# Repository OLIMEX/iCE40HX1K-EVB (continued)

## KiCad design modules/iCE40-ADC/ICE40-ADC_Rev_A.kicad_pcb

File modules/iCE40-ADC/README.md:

# Repository re-located here: https://github.com/OLIMEX/iCE40-ADC/tree/master

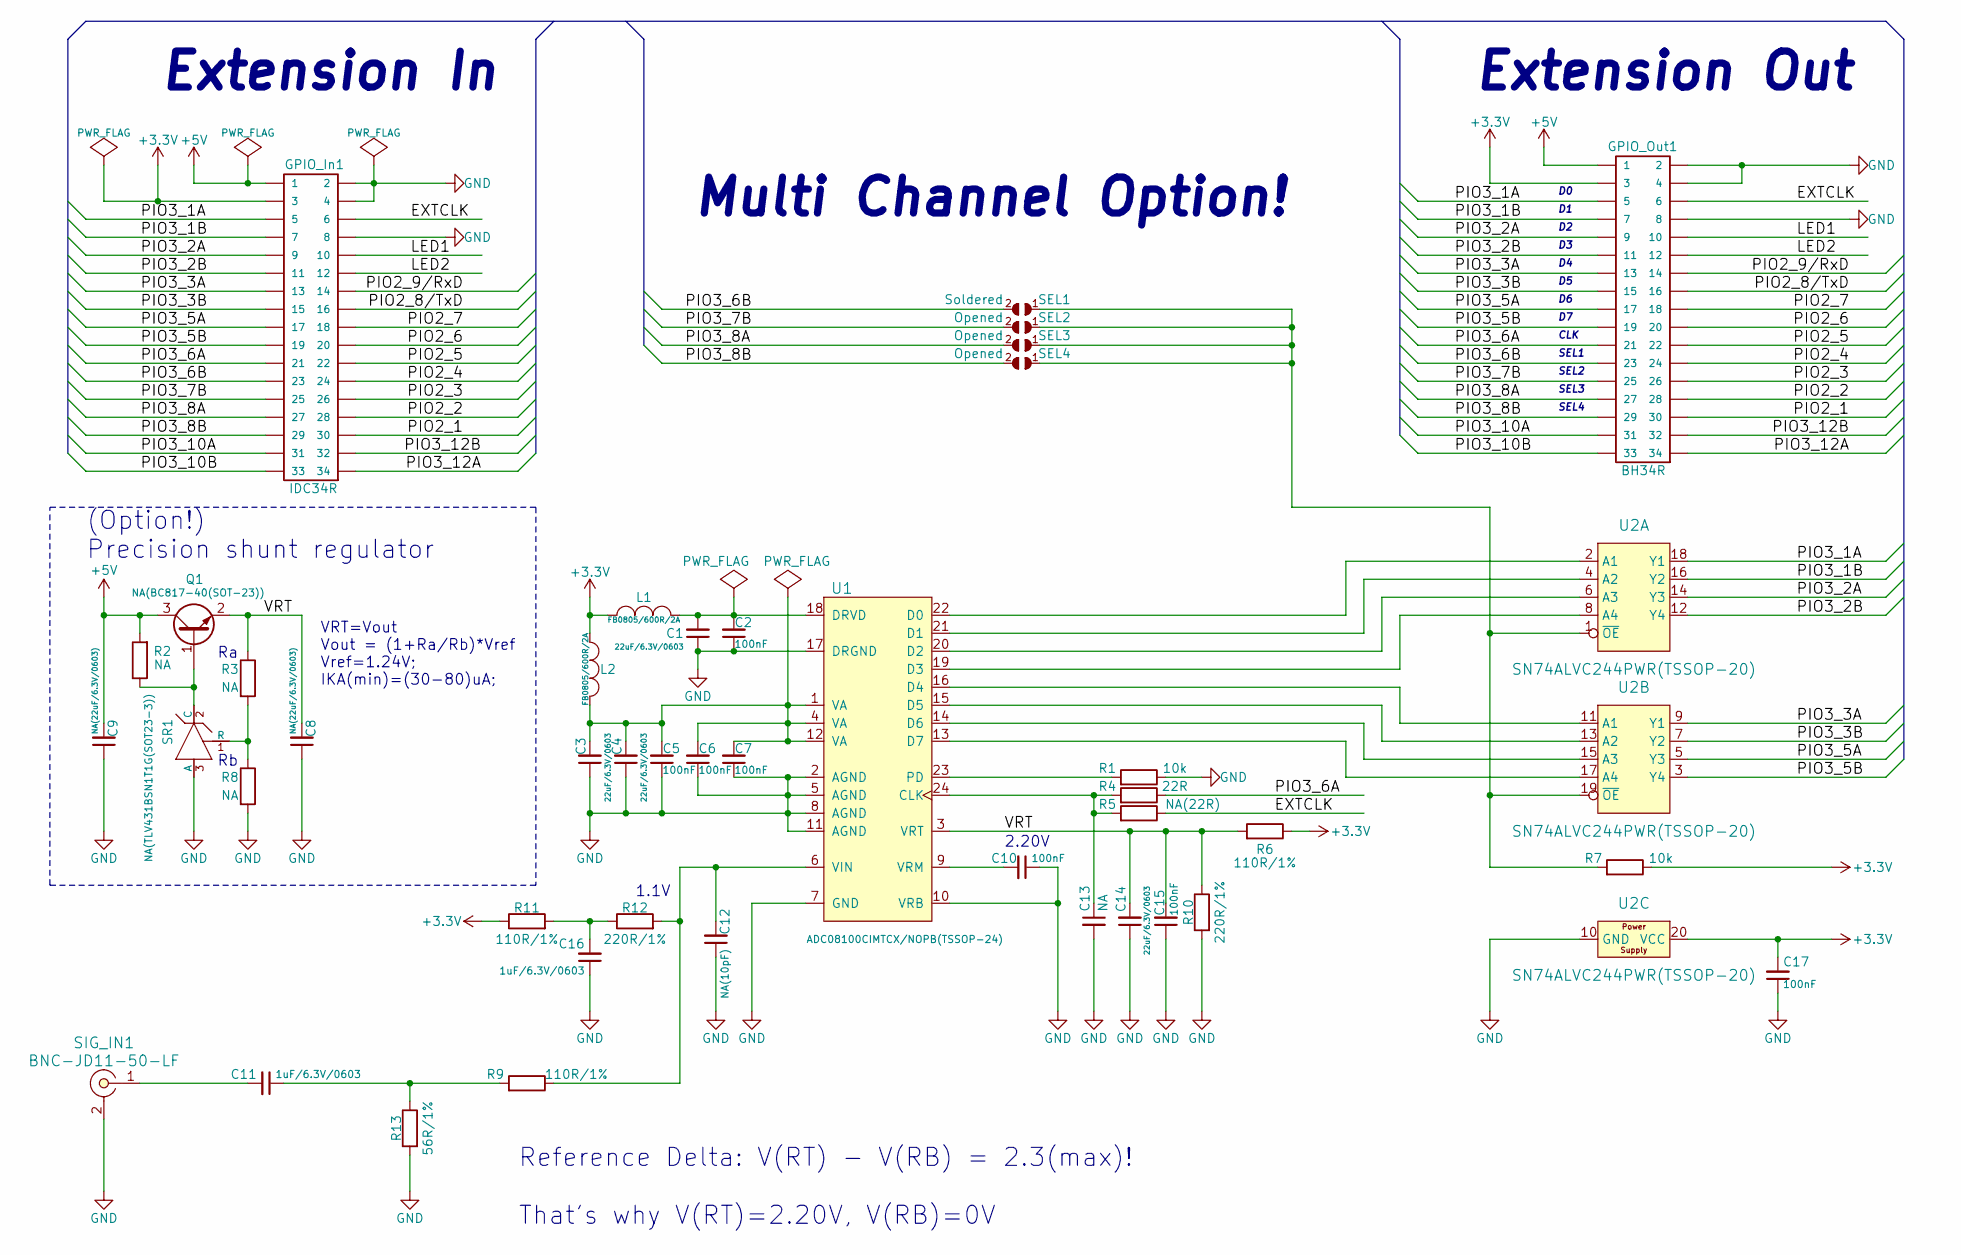
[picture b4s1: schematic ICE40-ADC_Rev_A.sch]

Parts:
C1, C3, C4, C14: 22uF/6.3V/0603; C_0603_5MIL_DWS
C2, C5, C6, C7, C10, C15, C17: 100nF; C_0402_5MIL_DWS
C8, C9: NA(22uF/6.3V/0603); C_0603_5MIL_DWS
C11, C16: 1uF/6.3V/0603; C_0603_5MIL_DWS
C12: NA(10pF); C_0402_5MIL_DWS
C13: NA; C_0402_5MIL_DWS
GPIO_In1: IDC34R; IDC34R_PCB
GPIO_Out1: BH34R
L1, L2: FB0805/600R/2A; L_0805_5MIL_DWS
Q1: NA(BC817-40(SOT-23)); SOT23
R1, R7: 10k; R_0402_5MIL_DWS
R2, R3, R8: NA; R_0402_5MIL_DWS
R4: 22R; R_0402_5MIL_DWS
R5: NA(22R); R_0402_5MIL_DWS
R6, R9, R11: 110R/1%; R_0402_5MIL_DWS
R10, R12: 220R/1%; R_0402_5MIL_DWS
R13: 56R/1%; R_0402_5MIL_DWS
SEL1: Soldered; SJ
SEL2, SEL3, SEL4: Opened; SJ
SIG_IN1: BNC-JD11-50-LF; BNC-JD11-50-LF_1-IN_2-GND
SR1: NA(TLV431BSN1T1G(SOT23-3)); SOT-23
U1: ADC08100CIMTCX/NOPB(TSSOP-24); TSSOP-24_Pitch-0.65mm_7.80x6.40x1.20mm
U2: SN74ALVC244PWR(TSSOP-20); TSSOP20_Pitch-0.65mm_6.6x4.5x1.2mm

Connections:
+3V3: C17.2, GPIO_In1.3, GPIO_Out1.3, L1.2, L2.2, R6.1, R7.1, R11.1, U2.20 (VCC)
+5V: C9.2, GPIO_In1.1, GPIO_Out1.1, Q1.3 (C), R2.2
/EXTCLK: GPIO_In1.6, GPIO_Out1.6, R5.1
/LED1: GPIO_In1.10, GPIO_Out1.10
/LED2: GPIO_In1.12, GPIO_Out1.12
/PIO2_1: GPIO_In1.30, GPIO_Out1.30
/PIO2_2: GPIO_In1.28, GPIO_Out1.28
/PIO2_3: GPIO_In1.26, GPIO_Out1.26
/PIO2_4: GPIO_In1.24, GPIO_Out1.24
/PIO2_5: GPIO_In1.22, GPIO_Out1.22
/PIO2_6: GPIO_In1.20, GPIO_Out1.20
/PIO2_7: GPIO_In1.18, GPIO_Out1.18
/PIO2_8/TxD: GPIO_In1.16, GPIO_Out1.16
/PIO2_9/RxD: GPIO_In1.14, GPIO_Out1.14
/PIO3_1A: GPIO_In1.5, GPIO_Out1.5, U2.18 (Y1)
/PIO3_1B: GPIO_In1.7, GPIO_Out1.7, U2.16 (Y2)
/PIO3_2A: GPIO_In1.9, GPIO_Out1.9, U2.14 (Y3)
/PIO3_2B: GPIO_In1.11, GPIO_Out1.11, U2.12 (Y4)
/PIO3_3A: GPIO_In1.13, GPIO_Out1.13, U2.9 (Y1)
/PIO3_3B: GPIO_In1.15, GPIO_Out1.15, U2.7 (Y2)
/PIO3_5A: GPIO_In1.17, GPIO_Out1.17, U2.5 (Y3)
/PIO3_5B: GPIO_In1.19, GPIO_Out1.19, U2.3 (Y4)
/PIO3_6A: GPIO_In1.21, GPIO_Out1.21, R4.1
/PIO3_6B: GPIO_In1.23, GPIO_Out1.23, SEL1.2
/PIO3_7B: GPIO_In1.25, GPIO_Out1.25, SEL2.2
/PIO3_8A: GPIO_In1.27, GPIO_Out1.27, SEL3.2
/PIO3_8B: GPIO_In1.29, GPIO_Out1.29, SEL4.2
/PIO3_10A: GPIO_In1.31, GPIO_Out1.31
/PIO3_10B: GPIO_In1.33, GPIO_Out1.33
/PIO3_12A: GPIO_In1.34, GPIO_Out1.34
/PIO3_12B: GPIO_In1.32, GPIO_Out1.32
/VRT: C8.2, C14.2, C15.2, Q1.2 (E), R3.1, R6.2, R10.1, U1.3 (VRT)
GND: C1.1, C2.1, C3.1, C4.1, C5.1, C6.1, C7.1, C8.1, C9.1, C10.1, C12.1, C13.2, C14.1, C15.1, C16.1, C17.1, GPIO_In1.2, GPIO_In1.4, GPIO_In1.8, GPIO_Out1.2, GPIO_Out1.4, GPIO_Out1.8, R1.1, R8.2, R10.2, R13.2, SIG_IN1.2, SR1.3 (A), U1.2 (AGND), U1.5 (AGND), U1.7 (GND), U1.8 (AGND), U1.10 (VRB), U1.11 (AGND), U1.17 (DRGND), U2.10 (GND)
unnamed: C1.2, C2.2, L1.1, U1.18 (DRVD)
unnamed: C3.2, C4.2, C5.2, C6.2, C7.2, L2.1, U1.1 (VA), U1.4 (VA), U1.12 (VA)
unnamed: C10.2, U1.9 (VRM)
unnamed: C11.1, R9.2, R13.1
unnamed: C11.2, SIG_IN1.1
unnamed: C12.2, R9.1, R12.2, U1.6 (VIN)
unnamed: C13.1, R4.2, R5.2, U1.24 (CLK)
unnamed: C16.2, R11.2, R12.1
unnamed: Q1.1 (B), R2.1, SR1.2 (C)
unnamed: R1.2, U1.23 (PD)
unnamed: R3.2, R8.1, SR1.1 (R)
unnamed: R7.2, SEL1.1, SEL2.1, SEL3.1, SEL4.1, U2.1 (~OE), U2.19 (~OE)
unnamed: U1.13 (D7), U2.17 (A4)
unnamed: U1.14 (D6), U2.15 (A3)
unnamed: U1.15 (D5), U2.13 (A2)
unnamed: U1.16 (D4), U2.11 (A1)
unnamed: U1.19 (D3), U2.8 (A4)
unnamed: U1.20 (D2), U2.6 (A3)
unnamed: U1.21 (D1), U2.4 (A2)
unnamed: U1.22 (D0), U2.2 (A1)

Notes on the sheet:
Extension Out
Extension In
VRT=Vout Vout = (1+Ra/Rb)*Vref Vref=1.24V; IKA(min)=(30-80)uA;
2.20V
1.1V
Reference Delta: V(RT) - V(RB) = 2.3(max)! That's why V(RT)=2.20V, V(RB)=0V
(Option!) Precision shunt regulator
Multi Channel Option!
CLK
SEL1
SEL2
SEL3
SEL4

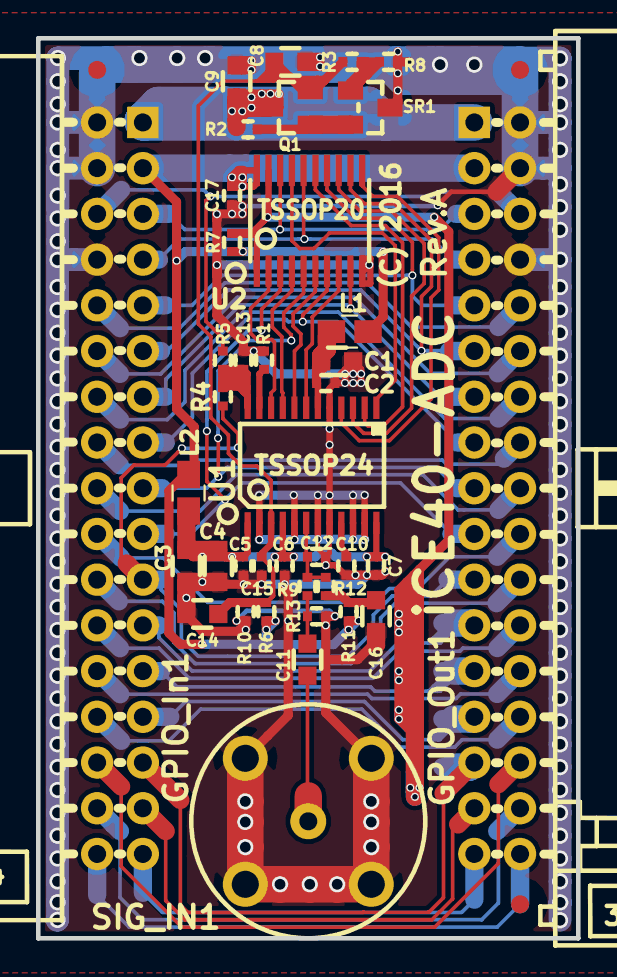
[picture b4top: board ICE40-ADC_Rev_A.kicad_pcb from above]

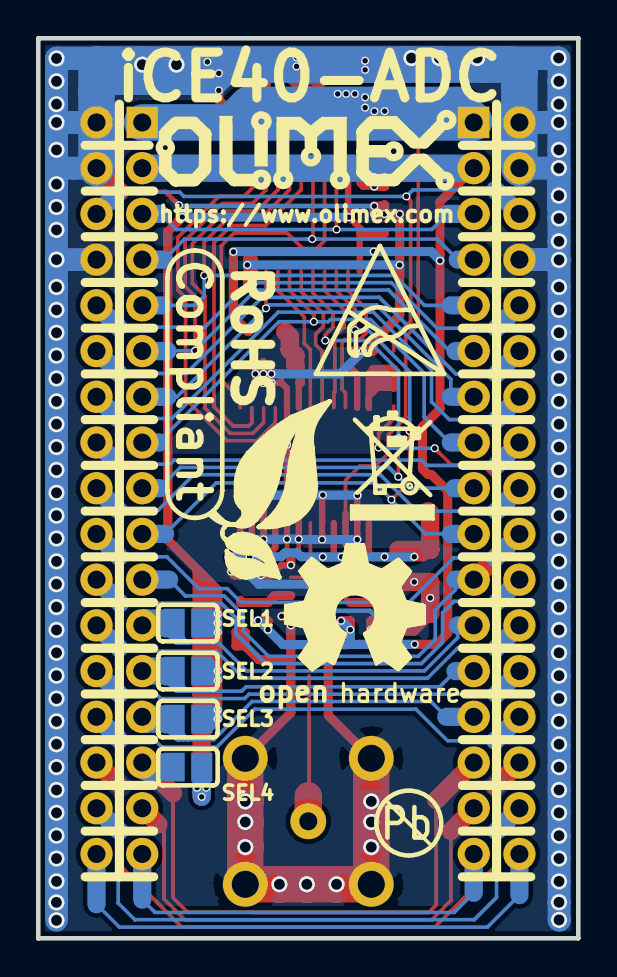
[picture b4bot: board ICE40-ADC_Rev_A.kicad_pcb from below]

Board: 2 copper layers, 30.0 x 50.0 mm, 45 parts (6 on the bottom side), 53 nets.

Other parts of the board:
Ref**: Val**; LOGO_ANTISTATIC_1
Ref**#2: Val**; LOGO_ROHS_1

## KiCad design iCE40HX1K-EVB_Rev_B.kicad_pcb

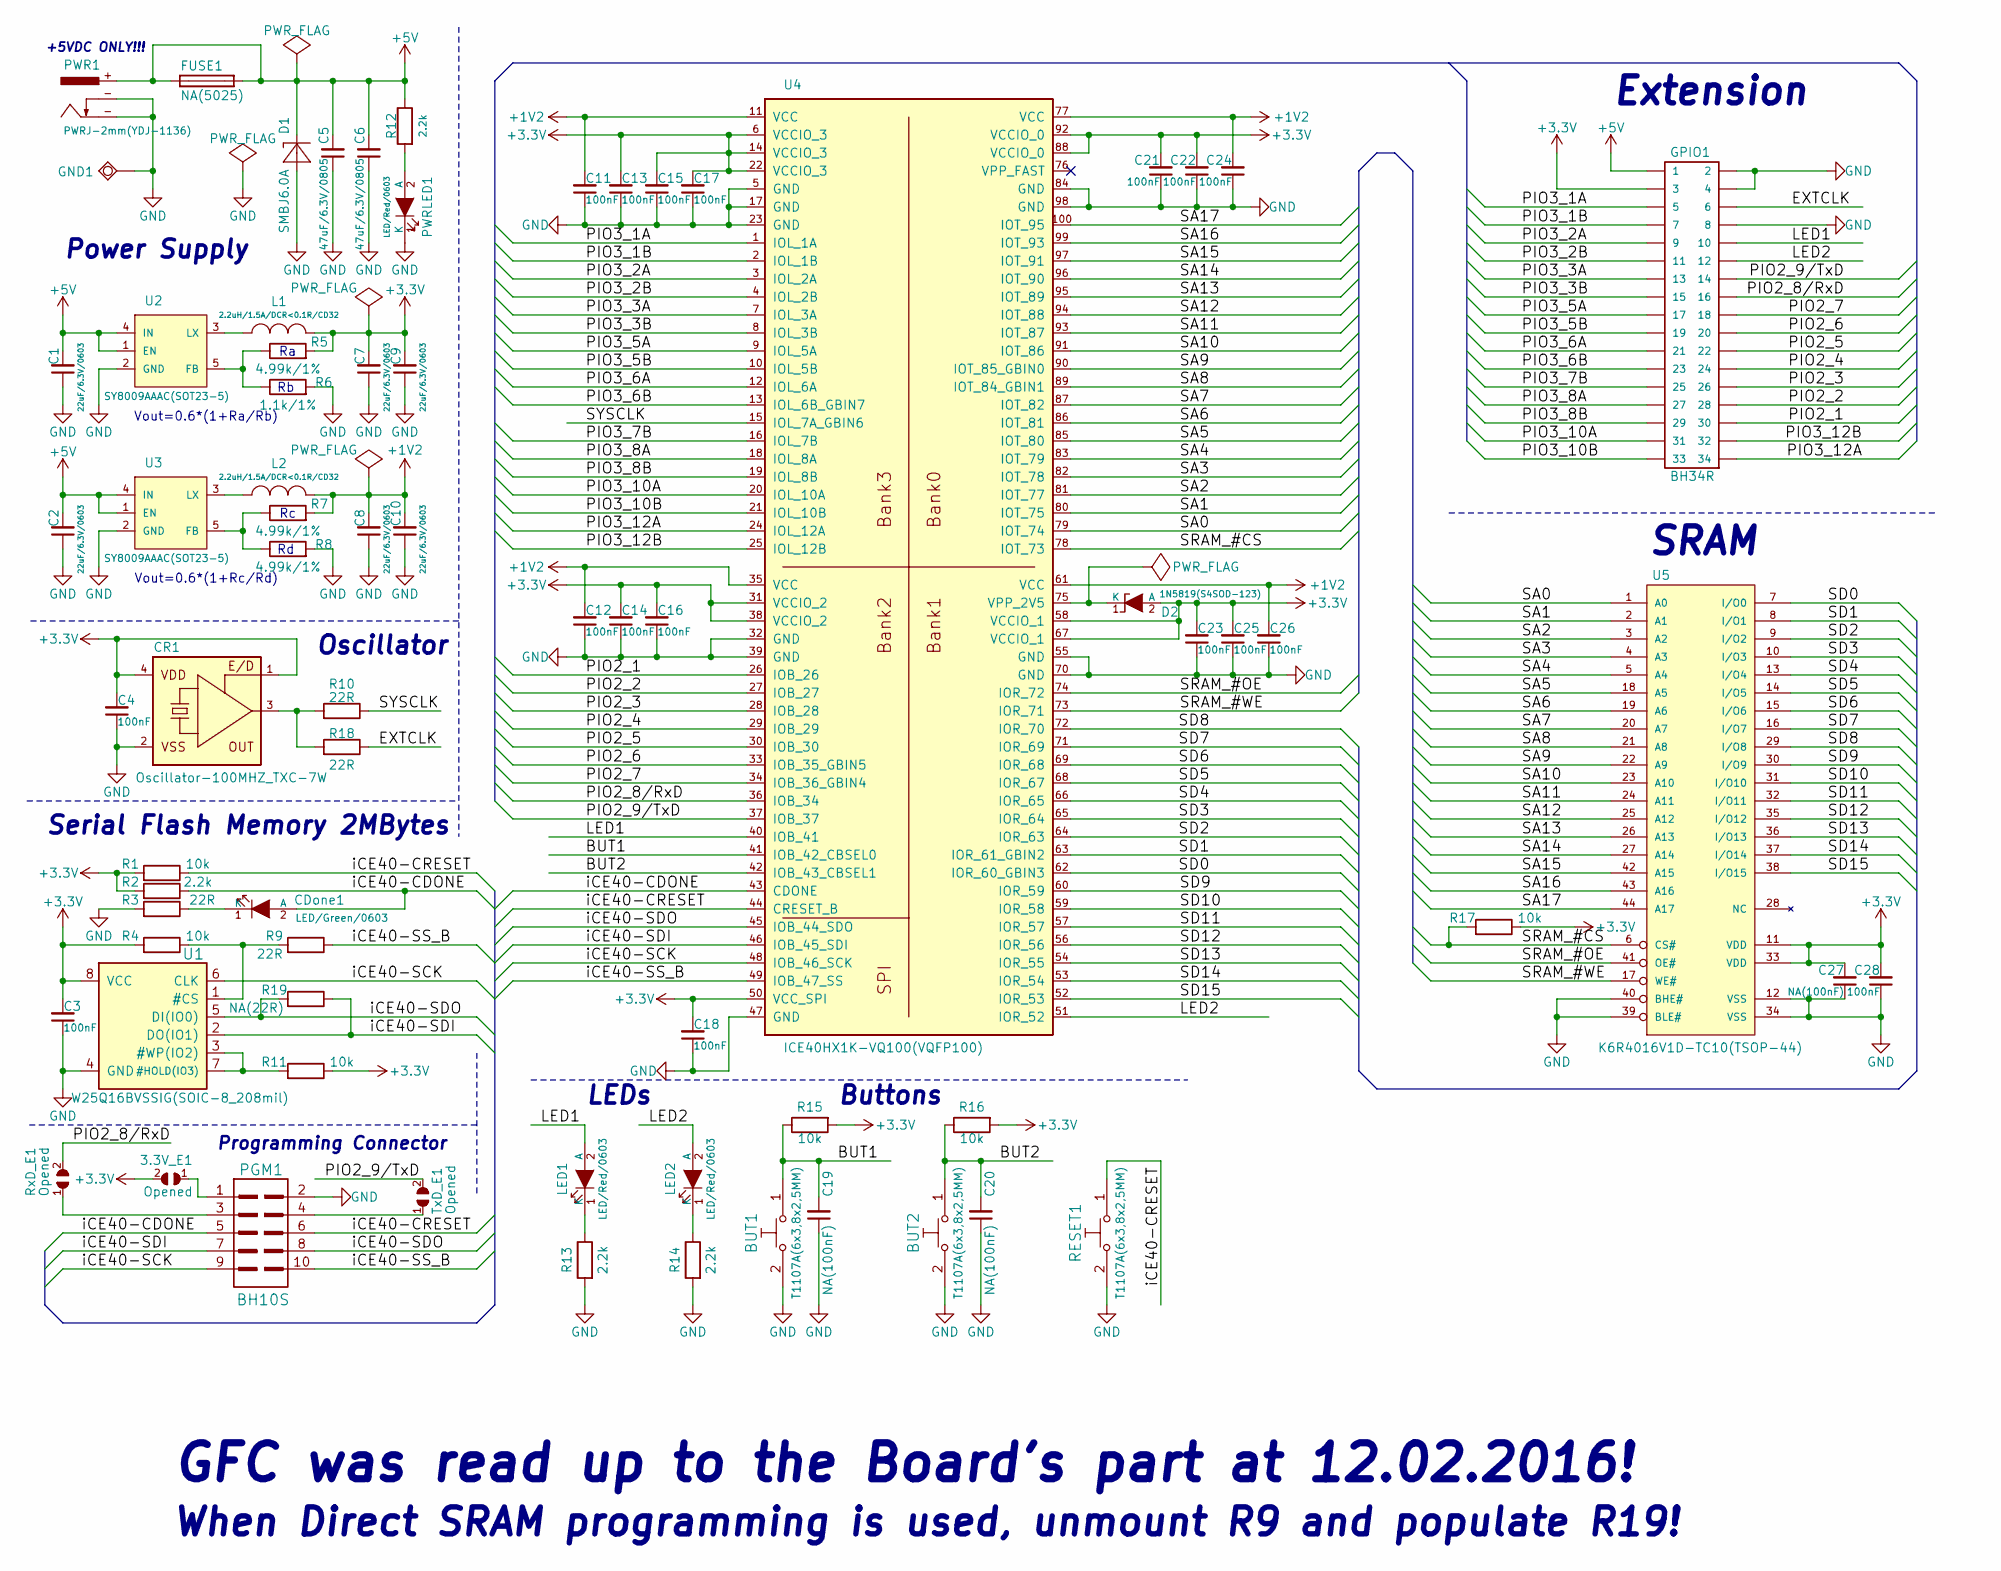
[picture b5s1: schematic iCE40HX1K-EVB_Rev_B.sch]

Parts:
3.3V_E1: Opened; SJ
BUT1, BUT2: T1107A(6x3,8x2,5MM)
C1, C2, C7, C8, C9, C10: 22uF/6.3V/0603; C_0603_5MIL_DWS
C3, C4, C11, C12, C13, C14, C15, C16, C17, C18, C21, C22, C23, C24, C25, C26, C28: 100nF; C_0402_5MIL_DWS
C5, C6: 47uF/6.3V/0805; C_0805_5MIL_DWS
C19, C20, C27: NA(100nF); C_0402_5MIL_DWS
CDone1: LED/Green/0603; LED_0603_KA
CR1: Oscillator-100MHZ_TXC-7W; Oscillator_7.0x5.0mm
D1: SMBJ6.0A; DO214AA
D2: 1N5819(S4SOD-123); SOD-123_1C-2A_KA
FUSE1: NA(5025); FUSE-5025
GND1: TESTPAD; TEST_PAD40x70_SQUARE
GPIO1: BH34R
L1, L2: 2.2uH/1.5A/DCR<0.1R/CD32; CD32
LED1, LED2: LED/Red/0603; LED_0603_KA
PGM1: BH10S; UEXT_ML10
PWR1: PWRJ-2mm(YDJ-1136)
PWRLED1: LED/Red/0603; LED_0603_KA
R1, R4, R11, R15, R16, R17: 10k; R_0402_5MIL_DWS
R2, R12, R13, R14: 2.2k; R_0402_5MIL_DWS
R3, R9, R10, R18: 22R; R_0402_5MIL_DWS
R5, R7, R8: 4.99k/1%; R_0402_5MIL_DWS
R6: 1.1k/1%; R_0402_5MIL_DWS
R19: NA(22R); R_0402_5MIL_DWS
RESET1: T1107A(6x3,8x2,5MM)
RxD_E1: Opened; SJ
TxD_E1: Opened; SJ
U1: W25Q16BVSSIG(SOIC-8_208mil); SO-8_208mil
U2, U3: SY8009AAAC(SOT23-5); SOT-23-5
U4: ICE40HX1K-VQ100(VQFP100); VQFP100_Pitch-0.5mm_Dimensions-16.00x16.00x1.20mm
U5: K6R4016V1D-TC10(TSOP-44); TSOP-44_Pitch-0.80mm_18.80x11.80x1.20mm

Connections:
+1V2: C8.2, C10.2, C11.2, C12.2, C24.2, C26.2, L2.1, R7.2, U4.11 (VCC), U4.35 (VCC), U4.61 (VCC), U4.77 (VCC)
+3V3: 3.3V_E1.2, C3.2, C4.2, C7.2, C9.2, C13.2, C14.2, C15.2, C16.2, C17.2, C18.2, C21.2, C22.2, C23.2, C25.2, C27.2, C28.2, CR1.1 (E/D), CR1.4 (VDD), D2.2 (A), GPIO1.3, L1.1, R1.2, R2.2, R4.2, R5.2, R11.1, R15.2, R16.2, R17.1, U1.8 (VCC), U4.6 (VCCIO_3), U4.14 (VCCIO_3), U4.22 (VCCIO_3), U4.31 (VCCIO_2), U4.38 (VCCIO_2), U4.50 (VCC_SPI), U4.58 (VCCIO_1), U4.67 (VCCIO_1), U4.88 (VCCIO_0), U4.92 (VCCIO_0), U5.11 (VDD), U5.33 (VDD)
+5V: C1.2, C2.2, C5.2, C6.2, D1.C, FUSE1.1, FUSE1.2, GPIO1.1, PWR1.+, R12.1, U2.1 (EN), U2.4 (IN), U3.1 (EN), U3.4 (IN)
/BUT1: BUT1.1, C19.2, R15.1, U4.41 (IOB_42_CBSEL0)
/BUT2: BUT2.1, C20.2, R16.1, U4.42 (IOB_43_CBSEL1)
/EXTCLK: GPIO1.6, R18.1
/LED1: GPIO1.10, LED1.2 (A), U4.40 (IOB_41)
/LED2: GPIO1.12, LED2.2 (A), U4.51 (IOR_52)
/PIO2_1: GPIO1.30, U4.26 (IOB_26)
/PIO2_2: GPIO1.28, U4.27 (IOB_27)
/PIO2_3: GPIO1.26, U4.28 (IOB_28)
/PIO2_4: GPIO1.24, U4.29 (IOB_29)
/PIO2_5: GPIO1.22, U4.30 (IOB_30)
/PIO2_6: GPIO1.20, U4.33 (IOB_35_GBIN5)
/PIO2_7: GPIO1.18, U4.34 (IOB_36_GBIN4)
/PIO2_8/RxD: GPIO1.16, RxD_E1.2, U4.36 (IOB_34)
/PIO2_9/TxD: GPIO1.14, TxD_E1.2, U4.37 (IOB_37)
/PIO3_1A: GPIO1.5, U4.1 (IOL_1A)
/PIO3_1B: GPIO1.7, U4.2 (IOL_1B)
/PIO3_2A: GPIO1.9, U4.3 (IOL_2A)
/PIO3_2B: GPIO1.11, U4.4 (IOL_2B)
/PIO3_3A: GPIO1.13, U4.7 (IOL_3A)
/PIO3_3B: GPIO1.15, U4.8 (IOL_3B)
/PIO3_5A: GPIO1.17, U4.9 (IOL_5A)
/PIO3_5B: GPIO1.19, U4.10 (IOL_5B)
/PIO3_6A: GPIO1.21, U4.12 (IOL_6A)
/PIO3_6B: GPIO1.23, U4.13 (IOL_6B_GBIN7)
/PIO3_7B: GPIO1.25, U4.16 (IOL_7B)
/PIO3_8A: GPIO1.27, U4.18 (IOL_8A)
/PIO3_8B: GPIO1.29, U4.19 (IOL_8B)
/PIO3_10A: GPIO1.31, U4.20 (IOL_10A)
/PIO3_10B: GPIO1.33, U4.21 (IOL_10B)
/PIO3_12A: GPIO1.34, U4.24 (IOL_12A)
/PIO3_12B: GPIO1.32, U4.25 (IOL_12B)
/SA0: U4.79 (IOT_74), U5.1 (A0)
/SA1: U4.80 (IOT_75), U5.2 (A1)
/SA2: U4.81 (IOT_77), U5.3 (A2)
/SA3: U4.82 (IOT_78), U5.4 (A3)
/SA4: U4.83 (IOT_79), U5.5 (A4)
/SA5: U4.85 (IOT_80), U5.18 (A5)
/SA6: U4.86 (IOT_81), U5.19 (A6)
/SA7: U4.87 (IOT_82), U5.20 (A7)
/SA8: U4.89 (IOT_84_GBIN1), U5.21 (A8)
/SA9: U4.90 (IOT_85_GBIN0), U5.22 (A9)
/SA10: U4.91 (IOT_86), U5.23 (A10)
/SA11: U4.93 (IOT_87), U5.24 (A11)
/SA12: U4.94 (IOT_88), U5.25 (A12)
/SA13: U4.95 (IOT_89), U5.26 (A13)
/SA14: U4.96 (IOT_90), U5.27 (A14)
/SA15: U4.97 (IOT_91), U5.42 (A15)
/SA16: U4.99 (IOT_93), U5.43 (A16)
/SA17: U4.100 (IOT_95), U5.44 (A17)
/SD0: U4.62 (IOR_60_GBIN3), U5.7 (I/O0)
/SD1: U4.63 (IOR_61_GBIN2), U5.8 (I/O1)
/SD2: U4.64 (IOR_63), U5.9 (I/O2)
/SD3: U4.65 (IOR_64), U5.10 (I/O3)
/SD4: U4.66 (IOR_65), U5.13 (I/O4)
/SD5: U4.68 (IOR_67), U5.14 (I/O5)
/SD6: U4.69 (IOR_68), U5.15 (I/O6)
/SD7: U4.71 (IOR_69), U5.16 (I/O7)
/SD8: U4.72 (IOR_70), U5.29 (I/O8)
/SD9: U4.60 (IOR_59), U5.30 (I/O9)
/SD10: U4.59 (IOR_58), U5.31 (I/O10)
/SD11: U4.57 (IOR_57), U5.32 (I/O11)
/SD12: U4.56 (IOR_56), U5.35 (I/O12)
/SD13: U4.54 (IOR_55), U5.36 (I/O13)
/SD14: U4.53 (IOR_54), U5.37 (I/O14)
/SD15: U4.52 (IOR_53), U5.38 (I/O15)
/SRAM_#CS: R17.2, U4.78 (IOT_73), U5.6 (CS#)
/SRAM_#OE: U4.74 (IOR_72), U5.41 (OE#)
/SRAM_#WE: U4.73 (IOR_71), U5.17 (WE#)
/SYSCLK: R10.1, U4.15 (IOL_7A_GBIN6)
/iCE40-CDONE: CDone1.2 (A), PGM1.5, R2.1, U4.43 (CDONE)
/iCE40-CRESET: PGM1.6, R1.1, RESET1.1, U4.44 (CRESET_B)
/iCE40-SCK: PGM1.9, U1.6 (CLK), U4.48 (IOB_46_SCK)
/iCE40-SDI: PGM1.7, R19.1, U1.2 (DO(IO1)), U4.46 (IOB_45_SDI)
/iCE40-SDO: PGM1.8, R19.2, U1.5 (DI(IO0)), U4.45 (IOB_44_SDO)
/iCE40-SS_B: PGM1.10, R9.1, U4.49 (IOB_47_SS)
GND: BUT1.2, BUT2.2, C1.1, C2.1, C3.1, C4.1, C5.1, C6.1, C7.1, C8.1, C9.1, C10.1, C11.1, C12.1, C13.1, C14.1, C15.1, C16.1, C17.1, C18.1, C19.1, C20.1, C21.1, C22.1, C23.1, C24.1, C25.1, C26.1, C27.1, C28.1, CR1.2 (VSS), D1.A, GND1.1, GPIO1.2, GPIO1.4, GPIO1.8, PGM1.2, PWR1.-, PWRLED1.1 (K), R3.2, R6.2, R8.2, R13.2, R14.2, RESET1.2, U1.4 (GND), U2.2 (GND), U3.2 (GND), U4.5 (GND), U4.17 (GND), U4.23 (GND), U4.32 (GND), U4.39 (GND), U4.47 (GND), U4.55 (GND), U4.70 (GND), U4.84 (GND), U4.98 (GND), U5.12 (VSS), U5.34 (VSS), U5.39 (BLE#), U5.40 (BHE#)
unnamed: 3.3V_E1.1, PGM1.1
unnamed: CDone1.1 (K), R3.1
unnamed: CR1.3 (OUT), R10.2, R18.2
unnamed: D2.1 (K), U4.75 (VPP_2V5)
unnamed: L1.2, U2.3 (LX)
unnamed: L2.2, U3.3 (LX)
unnamed: LED1.1 (K), R13.1
unnamed: LED2.1 (K), R14.1
unnamed: PGM1.3, RxD_E1.1
unnamed: PGM1.4, TxD_E1.1
unnamed: PWRLED1.2 (A), R12.2
unnamed: R4.1, R9.2, U1.1 (#CS)
unnamed: R5.1, R6.1, U2.5 (FB)
unnamed: R7.1, R8.1, U3.5 (FB)
unnamed: R11.2, U1.3 (#WP(IO2)), U1.7 (#HOLD(IO3))

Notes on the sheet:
Power Supply
Vout=0.6*(1+Ra/Rb)
Extension
GFC was read up to the Board's part at 12.02.2016!
+5VDC ONLY!!!
Vout=0.6*(1+Rc/Rd)
SRAM
Oscillator
Serial Flash Memory 2MBytes
Programming Connector
LEDs
Buttons
When Direct SRAM programming is used, unmount R9 and populate R19!

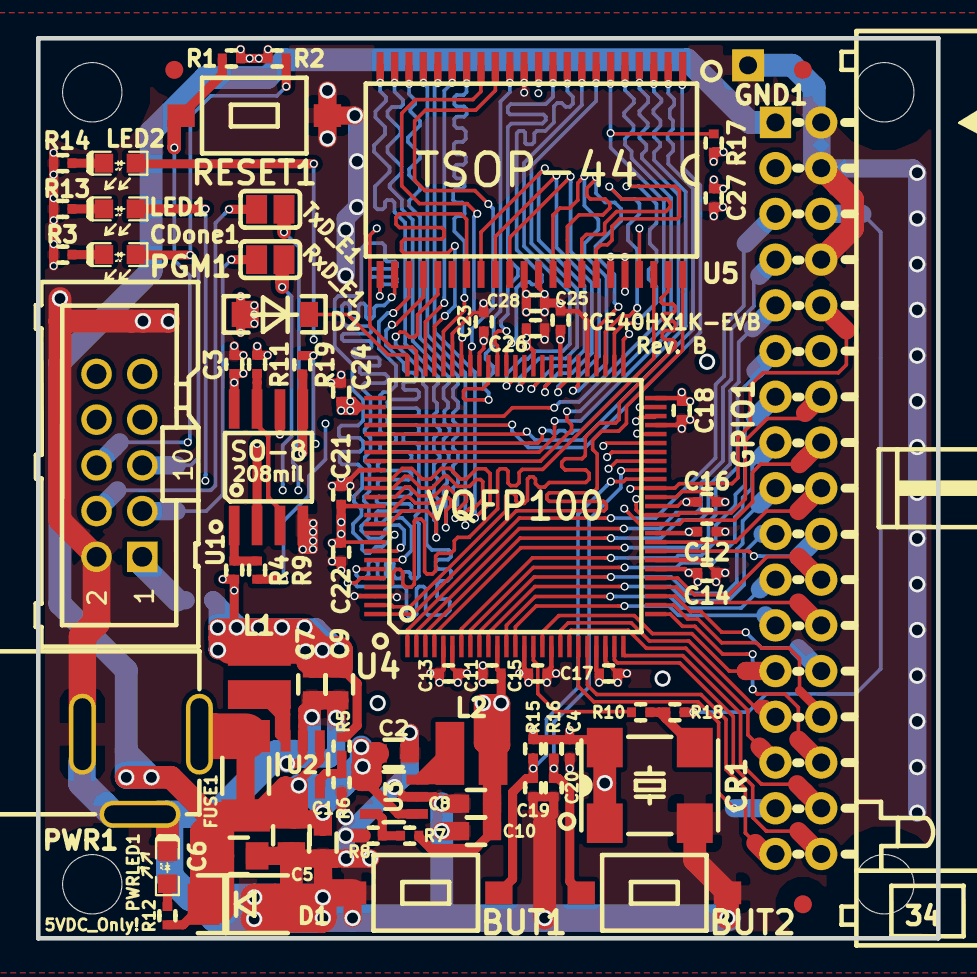
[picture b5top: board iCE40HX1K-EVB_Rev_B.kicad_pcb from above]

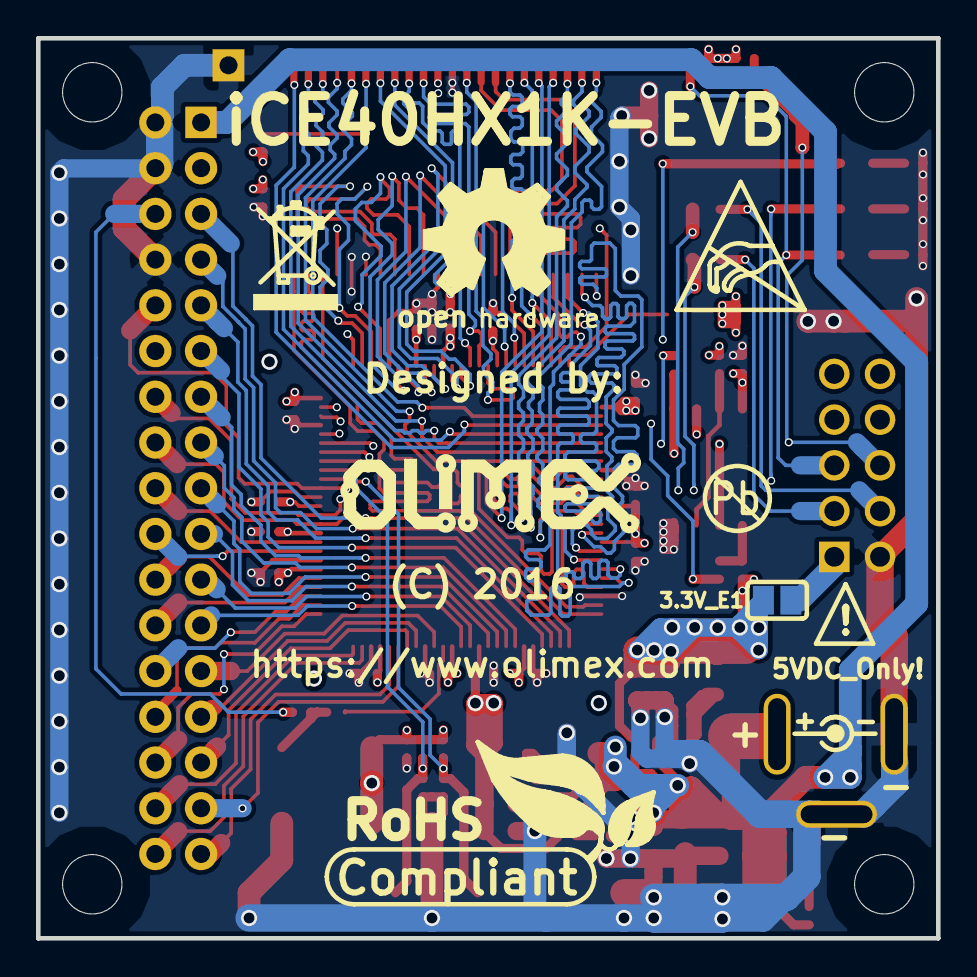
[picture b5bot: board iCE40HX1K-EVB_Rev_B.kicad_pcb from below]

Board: 4 copper layers, 50.0 x 50.0 mm, 78 parts (3 on the bottom side), 94 nets.

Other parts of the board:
MountingHole: Mounting_hole_3.3mm
MountingHole#2, MountingHole#3, MountingHole#4: Mounting_hole_3.3mm
Ref**: Val**; LOGO_ANTISTATIC_1
Ref**#2: Val**; LOGO_ROHS_1

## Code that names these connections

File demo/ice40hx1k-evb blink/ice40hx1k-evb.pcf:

set_io CLK 15
set_io BUT1 41
set_io BUT2 42
set_io LED1 40
set_io LED2 51

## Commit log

2016-02-12 initial schematic and pcb location
2016-06-30 Getting Started with ICESTORM, demo, board update
2016-07-12 update LED blink demo with more comments
2016-07-13 Add video generation tutorial
2016-07-15 iCE40 modules ADC, DAC, IO, DIO
2016-07-18 add blink LED iCEcube2 project for windows
2016-07-18 add winiceprogduino project
2016-07-19 improve VGA video example
2017-07-11 removed duplicates
2017-08-17 Add Windows users manual
2017-11-07 Add Adafruit Feather 32u4 as programmer
2018-03-12 Fix spelling errors in comments
    Column and Horizontally.
2019-01-13 iceprogduino: drop generated x86_64 binaries, add .gitignore
2019-01-13 programmer/olimexino-32u4 firmware: make it possible to use PlatformIO
    This commit simplifies firmware build by using PlatformIO (https://platformio.org/).
    PlatformIO makes it possible to build olimexino-32u4 firmware
    using CLI interface without manual Arduino libraries setup.
    SPIFlash library by Prajwal Bhattaram is outdated and is not available
    via current 1.8.8 Arduino IDE. SPIFlash has been superseded by SPIMemory.
    This commit imports SPIFlash 2.2.0 sources from SPIMemory github repo.
2020-01-24 iceprogduino: - added -o <offset in bytes> start address for write in bytes megabytes or kilobytes for iceprogduino - fix of flash_64kB_sector_erase
2020-05-26 added UART bridge
2022-04-01 fixing bug with platformio run compilation (undefined loop functions)
2022-09-20 Fix error in iceprog.cpp
2022-09-20 Revert untouched files
2023-10-05 Update
    Added pcf files for GPIO1
2026-01-14 Updated
    Added original firmware in case someone has trouble with the edited one (that utilizes buttons).
